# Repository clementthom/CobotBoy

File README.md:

# Organisation du répertoire de projet MECA22-3 (CobotCNJS)

Ce document retrace l'arborescence du répertoire de travail du groupe MECA22-3, travaillant sur le Cobot CNJS. Il fournit aussi quelques informations sur son contenu. Cette démarche a pour but de faciliter la navigation des personnes de l'équipe ou en lecture, et de ne pas égarer de documents.

## Code

Ce dossier rassemble l'ensemble du code produit par l'équipe, ainsi que sa documentation :

- **Archives** : contient du code archivé (non utilisé en l'état dans la version finale) ou des documents de travail ayant permis de créer la documentation finale
- **CODE_MEC22_3** : contient le code Arduino sous forme modulaire, facilitant la collaboration, la maintenabilité et la compréhension de ce dernier
- **Documentation** : contient l'intégralité de la documentation liée de près ou de loin au code et à ses choix technologiques. Sont englobés dans la documentation :
  - Le code et les ressources complètes liées au **dimensionnement du PID du système préhenseur**
  - Les **calculs mécaniques**, justifiant la conversion des coordonnées de l'objet en angles de commande pour les servomoteurs
  - Un compte rendu du **dimensionnement du PID**, résumant le travail effectué dans le dossier antérieur
  - Un **grafcet du cycle 2**
  - Un document .svg rassemblant tous les **schémas de représentation mécaniques du systèmes** ayant permis d'expliquer la conversion coordonnées/angles de commande
- **Terminal** : contient le code, les icônes et les exécutables de l'interface du terminal, accessible sur ordinateur, et permettant au Cobot CNJS d'entrer en mode maintenance
- **Lien GitHub** : fichier contenant les 2 liens liés à des répertoires GitHub liés au projet (ils sont à ce stade du projet obsolètes)

## Electronique

Ce dossier contient tout le travail effectué par l'équipe sur l'électronique, en particulier sur l'Interface Humain Machine (hors conception de l'identité graphique/UX) : 

- **Archives** : contient d'anciennes version de la carte de l'IHM 
- **boardDesign** : contient tous les fichiers liés à la conception de la carte
- **Documentation** : contient la documentation liée à cette conception, comme la **BOM**, le **bilan entrées-sorties et de puissance**, les **schémas du circuit électronique et de la carte**, ainsi que des captures d'écran représentant la carte en 3D
- un fichier compressé du **Gerber**, ainsi que des fichiers d'empreinte de l'encodeur rotatif

## Raccourci vers l'espace commun

Ce raccourci permet à l'équipe d'accéder en un clic aux ressources fournies par le client et par les experts.

## Gestion de projet

Ce dossier rassemble tous les outils de gestion de projet, incluant des **comptes rendus d'entrevues avec le client**, le **planning projet**, la banque horaire et autres fichiers similaires.

## Identité et communication

Ce dossier contient tout le travail en relation avec l'image de marque du projet, comme les fichiers de conception graphique de l'IHM, les versions successives des différents logos liés à CNJS, ainsi que la vidéo de présentation du système. On y retrouve aussi des ressources liées à la création de cette image, comme des rushs vidéos ou des fichiers d'édition vidéo.

## Manuels clients

Ce dossier contient les livrables à fournir au client qui ne peuvent être associés à un aspect du projet uniquement : 

- le **Manuel d'utilisation**
- le **Manuel de maintenance**

## Mécanique

Ce dossier contient tout le travail de conception et de calculs mécaniques, ainsi que les livrables et rendus associés : 

- **L'étude mécanique du 24/04/2026** : inclut le rapport d'étude dynamique et les plans de définitions finaux des préhenseurs
- **Mise en plan préhenseurs** : plans des préhenseurs antérieurs au 24 avril
- **Pièces 3D** : contient l'ensemble des pièces 3D produites par l'équipe (principalement en .step)
- **Le schéma cinématique du système**

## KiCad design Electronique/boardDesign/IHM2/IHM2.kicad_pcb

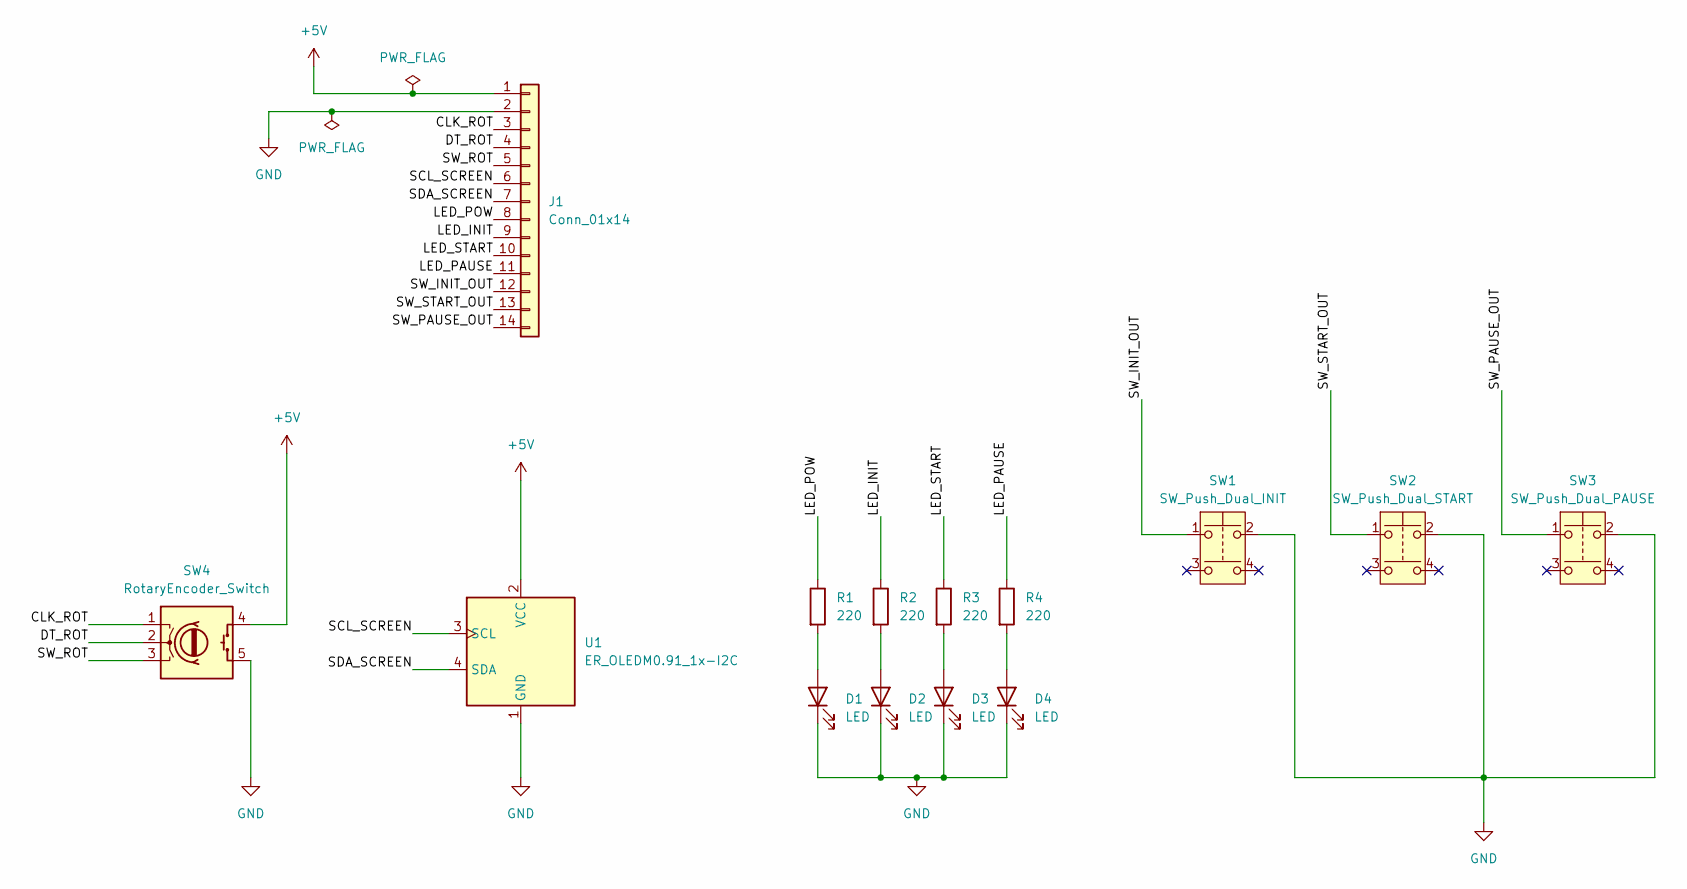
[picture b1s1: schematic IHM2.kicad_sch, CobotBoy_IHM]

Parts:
D1, D2, D3, D4: LED; LED_1206_3216Metric
J1: Conn_01x14; 1x14 THT input
R1, R2, R3, R4: 220; R_0805_2012Metric
SW1: SW_Push_Dual_INIT; SW_Push_Dual_13mm
SW2: SW_Push_Dual_START; SW_Push_Dual_13mm
SW3: SW_Push_Dual_PAUSE; SW_Push_Dual_13mm
SW4: RotaryEncoder_Switch; RotaryEncoder_SW
U1: ER_OLEDM0.91_1x-I2C; oledDisplay1Inch

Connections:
+5V: J1.1, SW4.4 (S1), U1.2 (VCC)
/CLK_ROT: J1.3, SW4.1 (CLK)
/DT_ROT: J1.4, SW4.2 (DT)
/LED_INIT: J1.9, R2.1
/LED_PAUSE: J1.11, R4.1
/LED_POW: J1.8, R1.1
/LED_START: J1.10, R3.1
/SCL_SCREEN: J1.6, U1.3 (SCL)
/SDA_SCREEN: J1.7, U1.4 (SDA)
/SW_INIT_OUT: J1.12, SW1.1
/SW_PAUSE_OUT: J1.14, SW3.1
/SW_ROT: J1.5, SW4.3 (SW)
/SW_START_OUT: J1.13, SW2.1
GND: D1.1 (K), D2.1 (K), D3.1 (K), D4.1 (K), J1.2, SW1.2, SW2.2, SW3.2, SW4.5 (S2), U1.1 (GND)
unnamed: D1.2 (A), R1.2
unnamed: D2.2 (A), R2.2
unnamed: D3.2 (A), R3.2
unnamed: D4.2 (A), R4.2

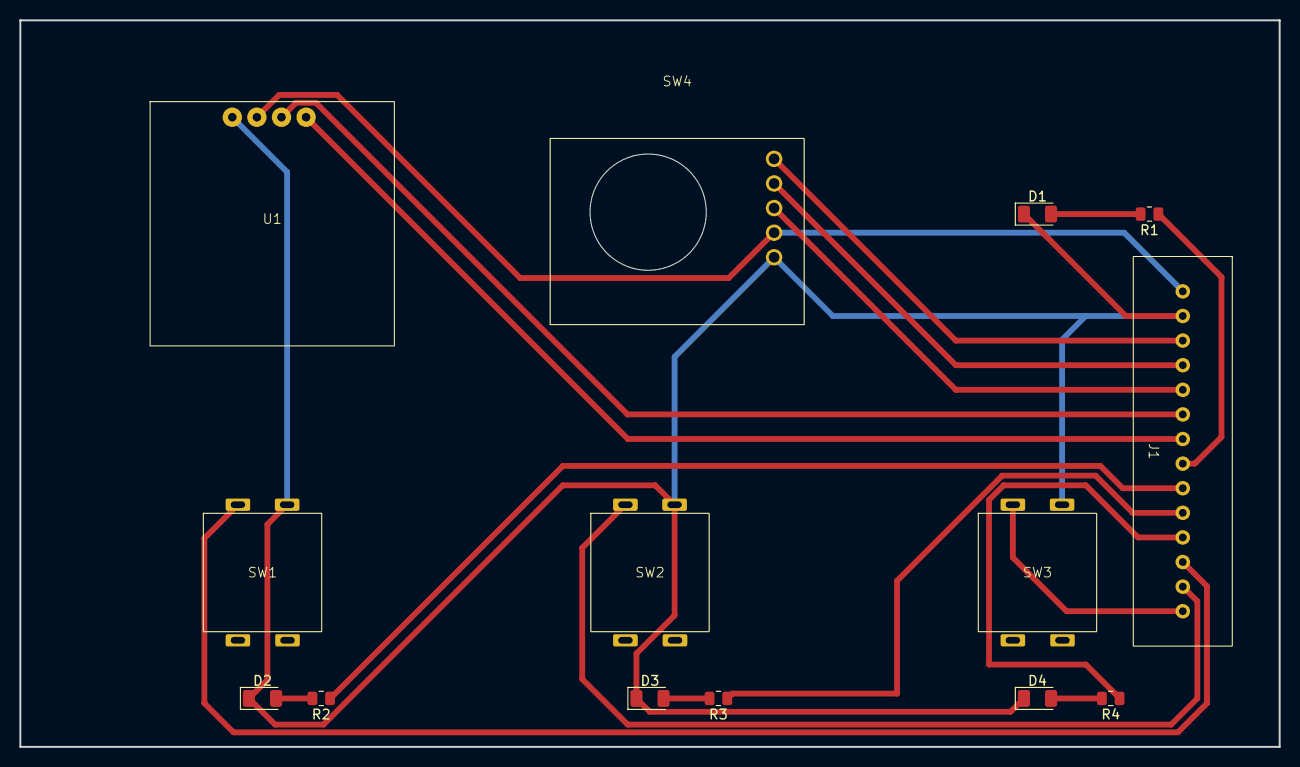
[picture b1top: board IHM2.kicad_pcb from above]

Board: 2 copper layers, 130.0 x 75.0 mm, 14 parts (0 on the bottom side), 18 nets.

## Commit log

2026-04-25 init : creation full project repo, not just code doc : links for PID control resources doc : determination of PID parameters using Octave models
2026-04-27 doc : new HMI with dimension chosen
2026-04-28 doc : remade graphs for PID in file to show that Td = 1000 in the related simulations feat : footprints and schematic for HMI done
2026-04-30 feat : creation of PCB HMI with corresponding schematics and footprints doc : created links list for online resources
2026-04-30 fix : added capacitors for power supply and I2C component refactor : removed via rollback : wrong IHM2 version (1 GND layer), recovered feat : added pin description on 1x14 pinset style : added logos
2026-05-01 refactor : included ToBeDefined criteria on capacitors
2026-05-01 fix : overlapping footprints build : created gerber folder + zip
2026-05-01 doc : created pdfs and pictures for the schematics and the PCB
2026-05-04 PCB -V4 ; no changes SCH fix : tracks separated even more from foreign components doc : updated PDFs build : updated Gerber + zip
2026-05-04 doc : added BOM doc : added input/output list without pins
2026-05-05 doc : added pins in input/output list
2026-05-07 ci : creation 3D file (step) for triangle obstacle
2026-05-08 doc = created documentation for PID regulation (not finished because lack of definitive PID parameters)
2026-05-12 ci : updated PID stydy folder to match the correction used in code doc : added readme for Drive repo
2026-05-19 ci : final commit
